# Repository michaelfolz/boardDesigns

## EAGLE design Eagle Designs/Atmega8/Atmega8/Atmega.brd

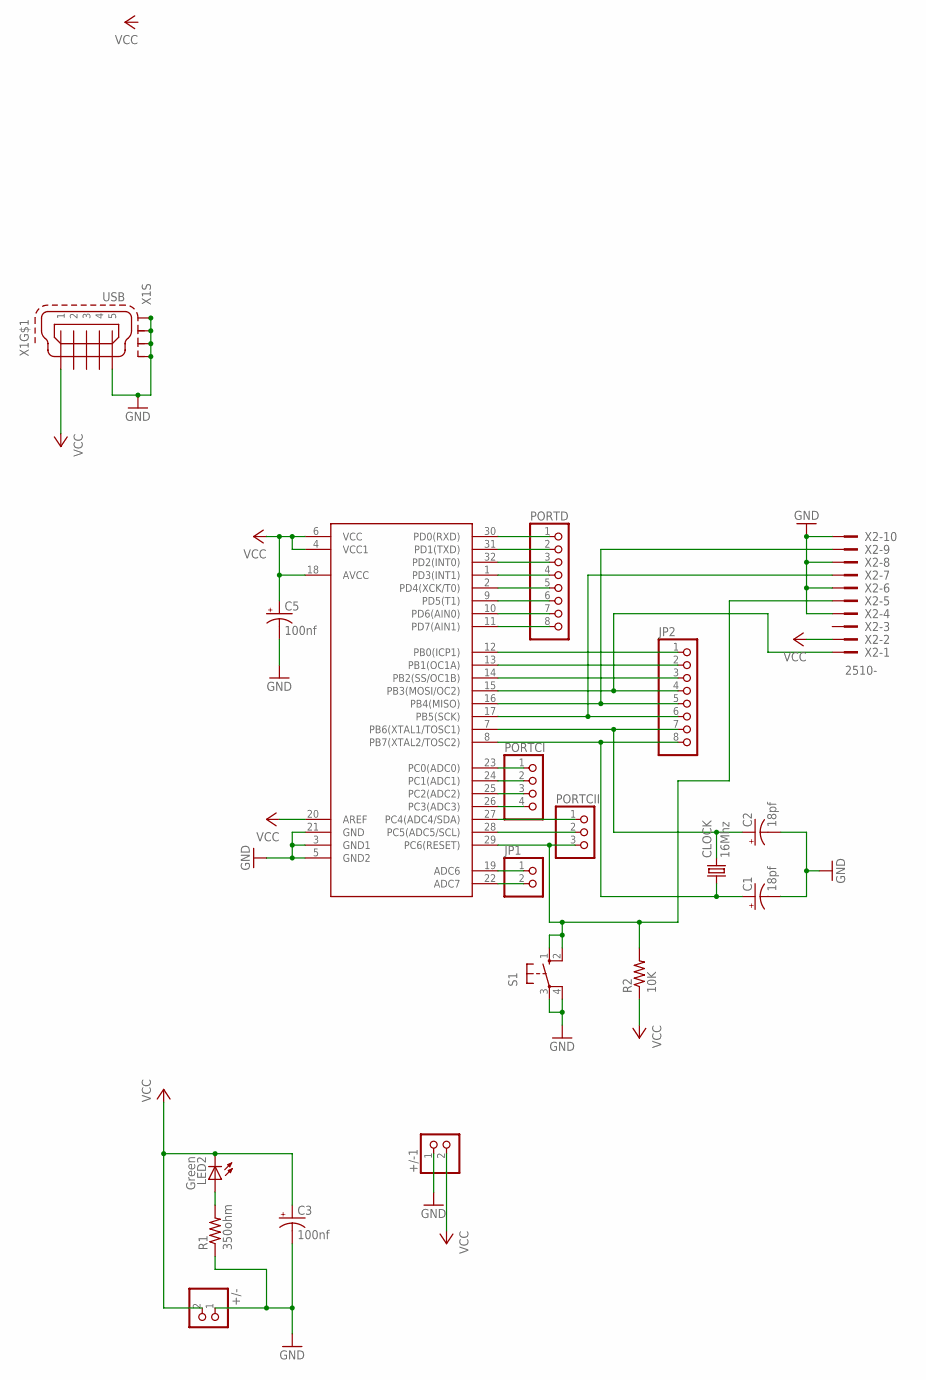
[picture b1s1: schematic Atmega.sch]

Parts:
+/-, +/-1: PINHD-1X2; 1X02
C1, C2: 18pf; SMC_Z
C3, C5: 100nf; SMC_Z
CLOCK: 16Mhz; HC49UP
JP1: PINHD-1X2; 1X02
JP2: PINHD-1X8; 1X08
LED2: Green; PLCC2
PORTCI: PINHD-1X4; 1X04
PORTCII: PINHD-1X3; 1X03
PORTD: PINHD-1X8; 1X08
R1: 350ohm; M0805
R2: 10K; M0805
S1: 10-XX; B3F-10XX
U$1: ATMEGA8A; TQFP32-08
X1: USB; 32005-201
X2: 2510-; PAK100/2500-10

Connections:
GND: +/-.1, +/-1.1, C1.-, C2.-, C3.-, C5.-, R1.1, S1.3, S1.4 (P1), U$1.3 (GND1), U$1.5 (GND2), U$1.21 (GND), X1.5, X1.M1 (S1), X1.M2 (S2), X1.M3 (S3), X1.M4 (S4), X2.4, X2.6, X2.8, X2.10
unnamed: LED2.A, R1.2
unnamed: PORTCI.1, U$1.23 (PC0(ADC0))
unnamed: PORTCI.2, U$1.24 (PC1(ADC1))
unnamed: PORTCI.3, U$1.25 (PC2(ADC2))
unnamed: PORTCI.4, U$1.26 (PC3(ADC3))
unnamed: PORTCII.1, U$1.27 (PC4(ADC4/SDA))
unnamed: PORTCII.2, U$1.28 (PC5(ADC5/SCL))
unnamed: PORTCII.3, R2.2, S1.1 (S), S1.2 (S1), U$1.29 (PC6(RESET)), X2.5
unnamed: JP2.1, U$1.12 (PB0(ICP1))
unnamed: JP2.2, U$1.13 (PB1(OC1A))
unnamed: JP2.3, U$1.14 (PB2(SS/OC1B))
unnamed: JP2.4, U$1.15 (PB3(MOSI/OC2)), X2.1
unnamed: JP2.5, U$1.16 (PB4(MISO)), X2.9
unnamed: JP2.6, U$1.17 (PB5(SCK)), X2.7
unnamed: C2.+, CLOCK.2, JP2.7, U$1.7 (PB6(XTAL1/TOSC1))
unnamed: C1.+, CLOCK.1, JP2.8, U$1.8 (PB7(XTAL2/TOSC2))
unnamed: PORTD.1, U$1.30 (PD0(RXD))
unnamed: PORTD.2, U$1.31 (PD1(TXD))
unnamed: PORTD.3, U$1.32 (PD2(INT0))
unnamed: PORTD.4, U$1.1 (PD3(INT1))
unnamed: PORTD.5, U$1.2 (PD4(XCK/T0))
unnamed: PORTD.6, U$1.9 (PD5(T1))
unnamed: PORTD.7, U$1.10 (PD6(AIN0))
unnamed: PORTD.8, U$1.11 (PD7(AIN1))
unnamed: JP1.1, U$1.19 (ADC6)
unnamed: JP1.2, U$1.22 (ADC7)
VCC: +/-.2, +/-1.2, C3.+, C5.+, LED2.C, R2.1, U$1.4 (VCC1), U$1.6 (VCC), U$1.18 (AVCC), U$1.20 (AREF), X1.1, X2.2

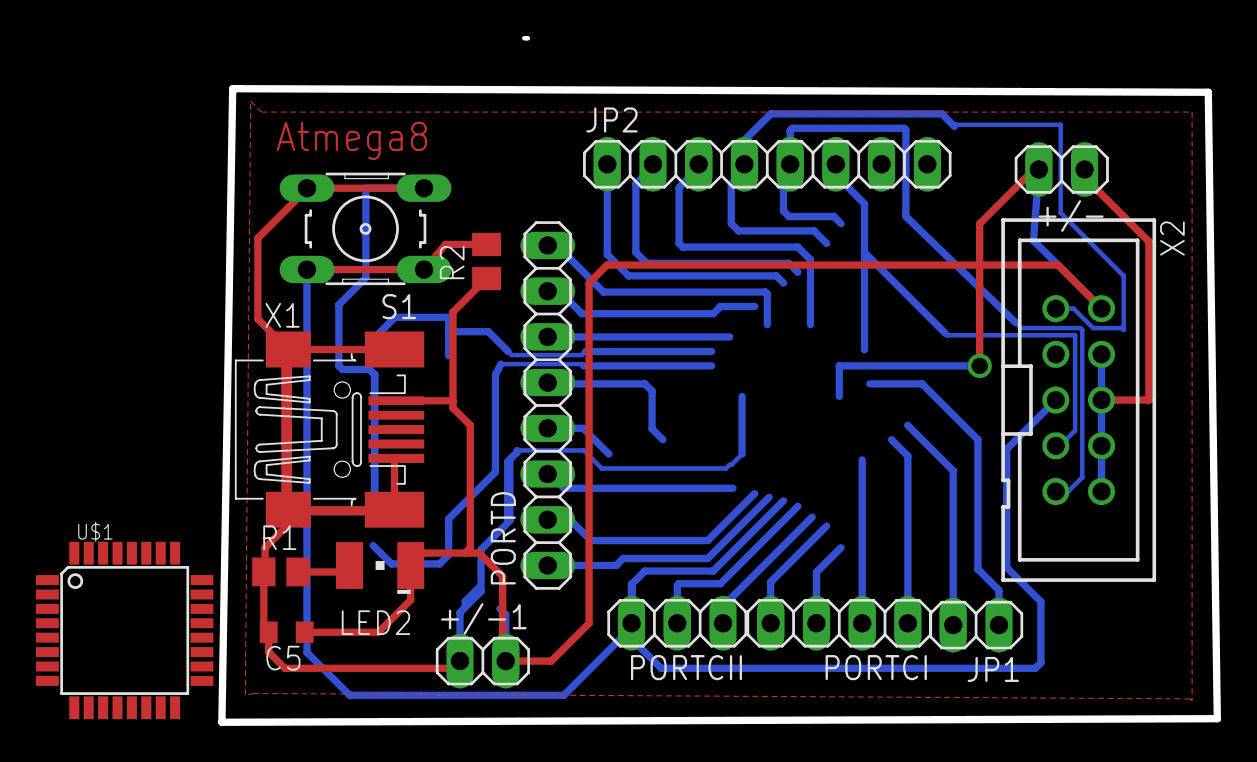
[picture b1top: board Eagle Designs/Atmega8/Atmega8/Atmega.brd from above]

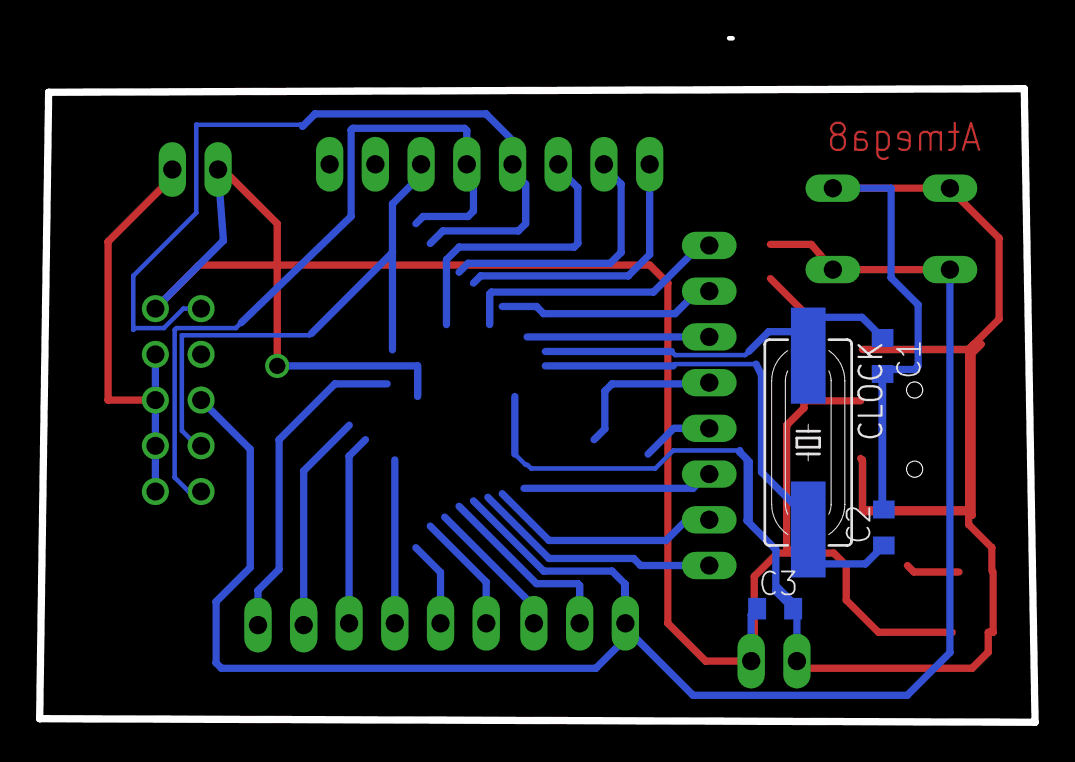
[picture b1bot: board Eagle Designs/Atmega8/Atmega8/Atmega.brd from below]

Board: 2 copper layers, 55.3 x 37.9 mm, 19 parts (4 on the bottom side), 28 nets.

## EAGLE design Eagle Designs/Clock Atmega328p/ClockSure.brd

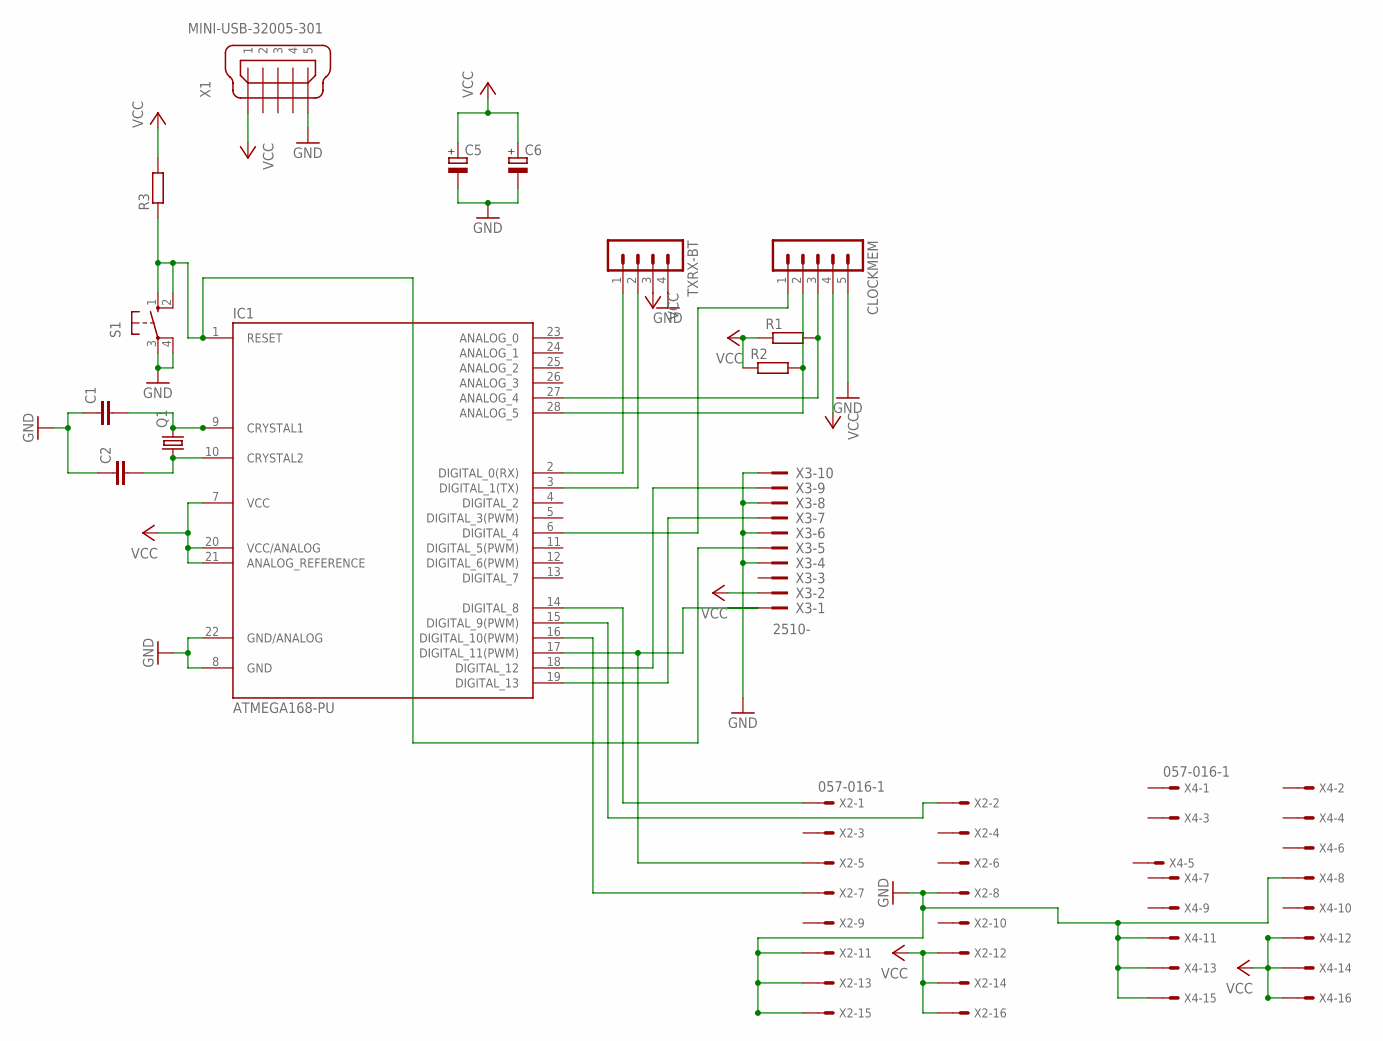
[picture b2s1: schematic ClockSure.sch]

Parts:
C1, C2: C-EU025-030X050; C025-030X050
C5, C6: CPOL-EUE2.5-6; E2,5-6
CLOCKMEM: MA05-1
IC1: ATMEGA168-PU; DIL28-3
Q1: CRYSTALHC49U70; HC49U70
R1, R2, R3: R-EU_0207/10; 0207/10
S1: 10-XX; B3F-10XX
TXRX-BT: MA04-1
X1: MINI-USB-32005-301; 32005-301
X2, X4: 057-016-1
X3: 2510-; PAK100/2500-10

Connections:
GND: C1.1, C2.1, C5.-, C6.-, CLOCKMEM.5, IC1.8 (GND), IC1.22 (GND/ANALOG), S1.3, S1.4 (P1), TXRX-BT.4, X1.5, X2.8, X2.11, X2.13, X2.15, X3.4, X3.6, X3.8, X3.10, X4.8, X4.11, X4.13, X4.15
unnamed: C1.2, IC1.9 (CRYSTAL1), Q1.2
unnamed: C2.2, IC1.10 (CRYSTAL2), Q1.1
unnamed: IC1.2 (DIGITAL_0(RX)), TXRX-BT.1
unnamed: IC1.3 (DIGITAL_1(TX)), TXRX-BT.2
unnamed: CLOCKMEM.2, IC1.28 (ANALOG_5), R2.2
unnamed: IC1.1 (RESET), R3.1, S1.1 (S), S1.2 (S1), X3.5
unnamed: CLOCKMEM.3, IC1.27 (ANALOG_4), R1.2
unnamed: IC1.18 (DIGITAL_12), X3.9
unnamed: IC1.19 (DIGITAL_13), X3.7
unnamed: IC1.17 (DIGITAL_11(PWM)), X2.5, X3.1
unnamed: IC1.15 (DIGITAL_9(PWM)), X2.2
unnamed: IC1.14 (DIGITAL_8), X2.1
unnamed: CLOCKMEM.1, IC1.6 (DIGITAL_4)
unnamed: IC1.16 (DIGITAL_10(PWM)), X2.7
VCC: C5.+, C6.+, CLOCKMEM.4, IC1.7 (VCC), IC1.20 (VCC/ANALOG), IC1.21 (ANALOG_REFERENCE), R1.1, R2.1, R3.2, TXRX-BT.3, X1.1, X2.12, X2.14, X2.16, X3.2, X4.12, X4.14, X4.16

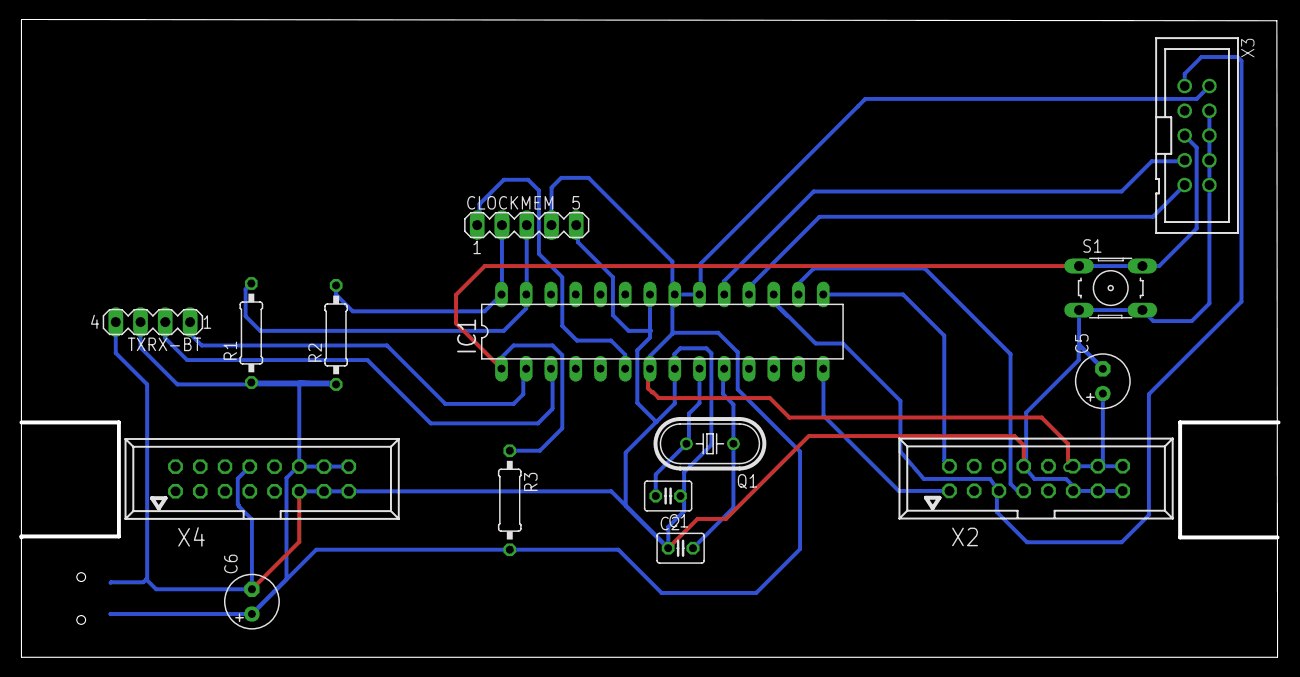
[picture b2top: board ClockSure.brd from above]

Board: 2 copper layers, 129.0 x 65.0 mm, 16 parts (1 on the bottom side), 16 nets.

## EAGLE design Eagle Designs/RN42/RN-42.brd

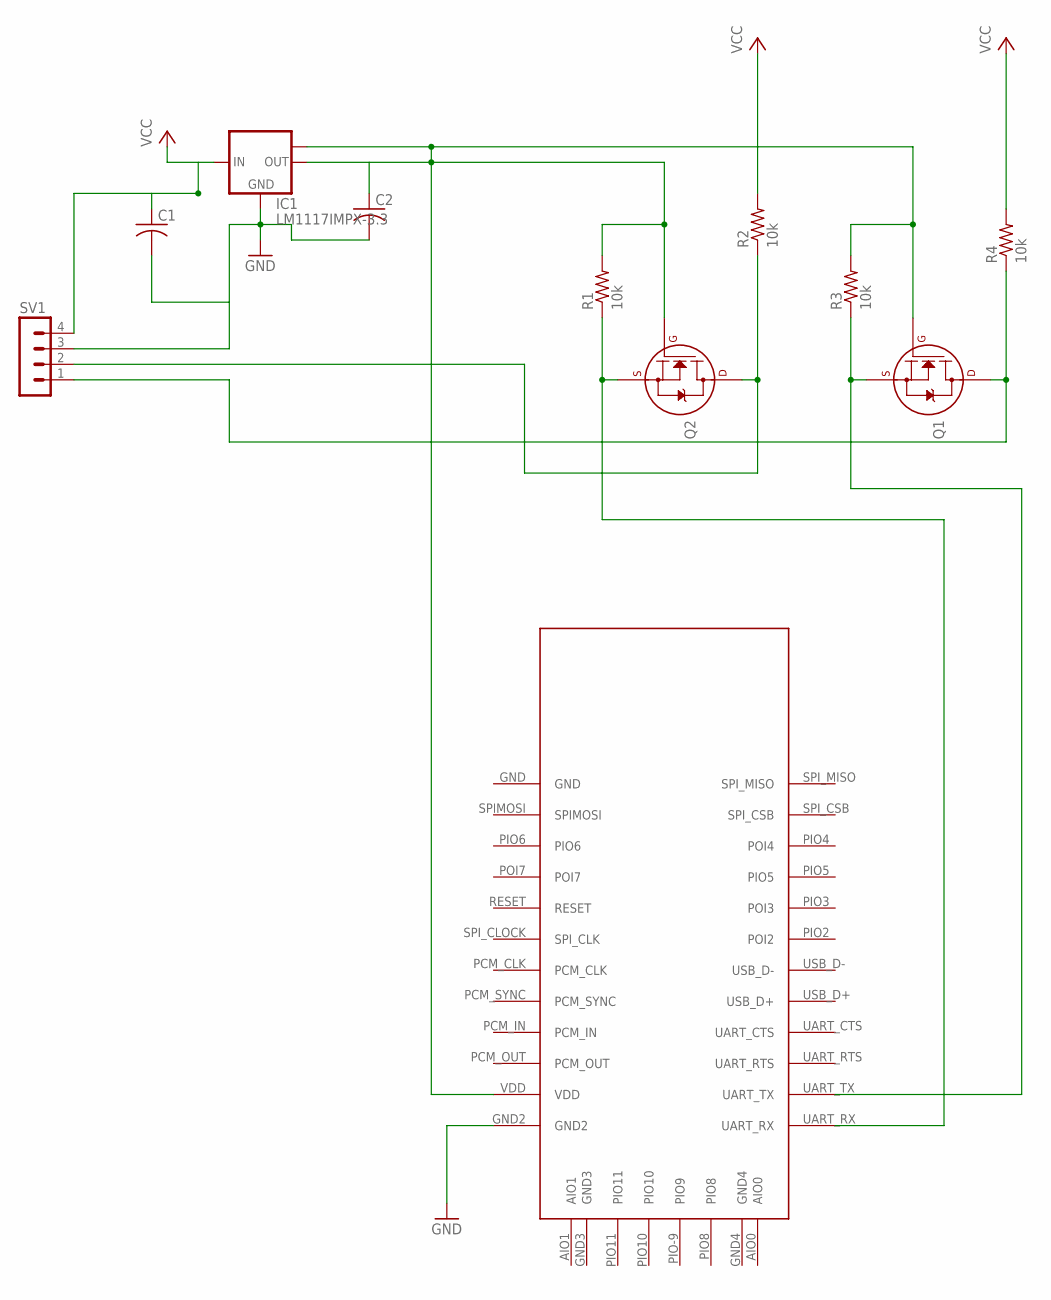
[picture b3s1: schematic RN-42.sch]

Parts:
C1, C2: C-USC0805; C0805
IC1: LM1117IMPX-3.3; SOT223
Q1, Q2: 2N7002_SOT23; SOT-23
R1, R2, R3, R4: 10k; M0805
SV1: MA04-1
U$1: RN-42

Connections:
GND: C1.2, C2.2, IC1.1 (GND), SV1.3, U$1.GND2
unnamed: Q2.2 (S), R1.1, U$1.UART_RX
unnamed: Q2.3 (D), R2.1, SV1.2
unnamed: Q1.2 (S), R3.1, U$1.UART_TX
unnamed: Q1.3 (D), R4.1, SV1.1
unnamed: C2.1, IC1.2 (OUT), IC1.TAB (OUT1), Q1.1 (G), Q2.1 (G), R1.2, R3.2, U$1.VDD
VCC: C1.1, IC1.3 (IN), R2.2, R4.2, SV1.4

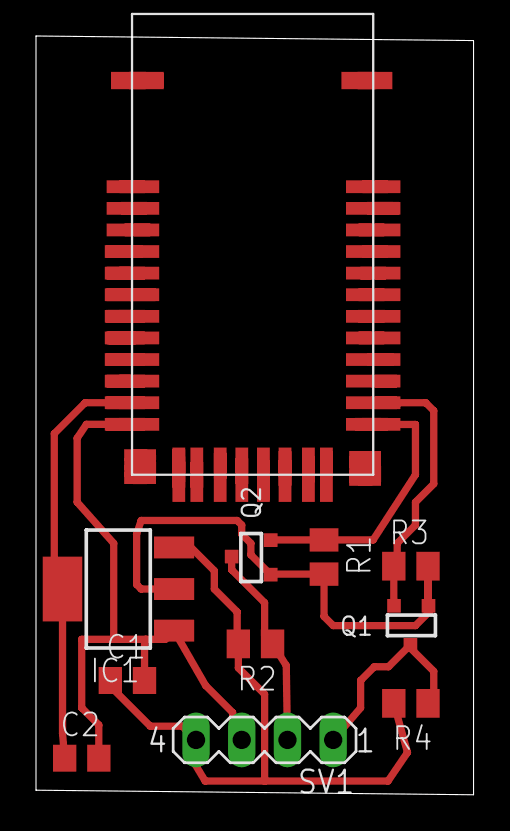
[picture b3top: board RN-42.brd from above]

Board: 2 copper layers, 24.3 x 42.2 mm, 11 parts (0 on the bottom side), 7 nets.

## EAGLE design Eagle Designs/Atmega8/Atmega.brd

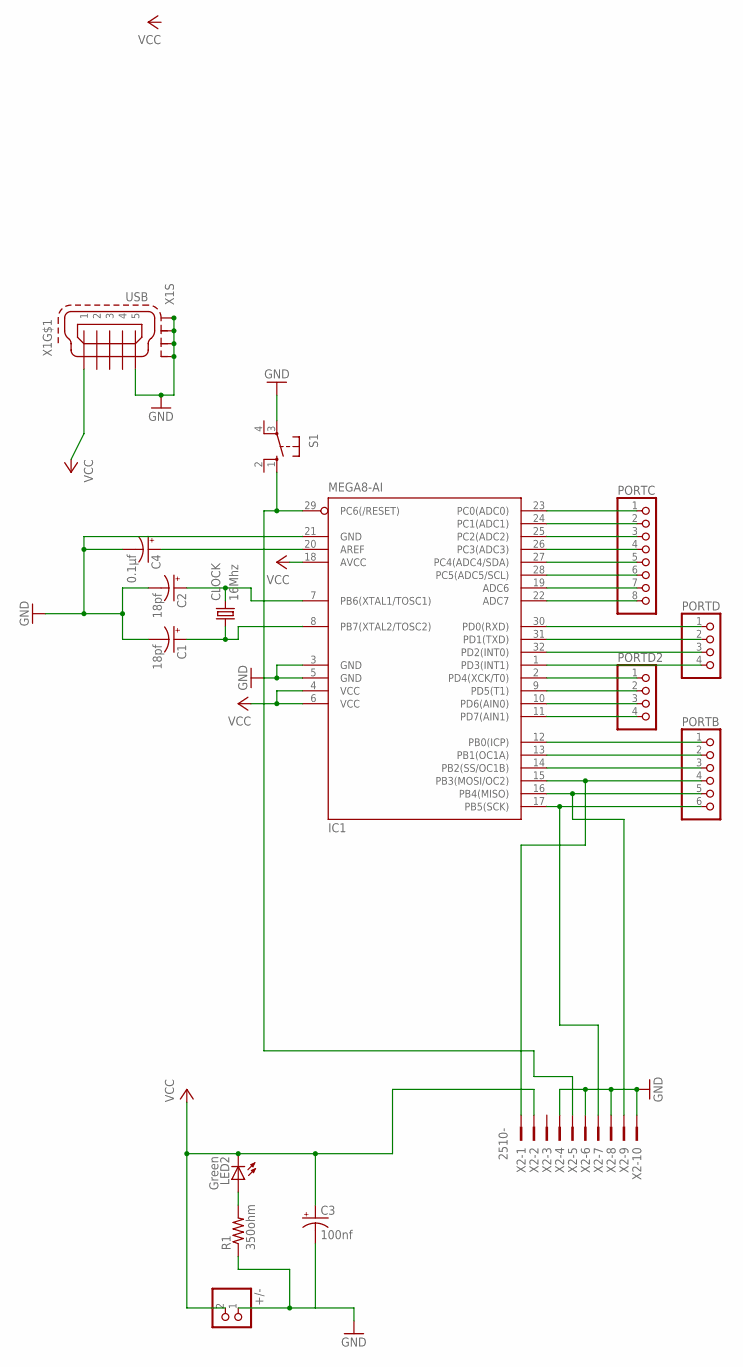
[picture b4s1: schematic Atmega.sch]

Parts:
+/-: PINHD-1X2; 1X02
C1, C2: 18pf; SMC_Z
C3: 100nf; SMC_Z
C4: 0.1µf; SMC_Z
CLOCK: 16Mhz; HC49UP
IC1: MEGA8-AI; TQFP32-08
LED2: Green; PLCC2
PORTB: PINHD-1X6; 1X06
PORTC: PINHD-1X8; 1X08
PORTD, PORTD2: PINHD-1X4; 1X04
R1: 350ohm; M0805
S1: 10-XX; B3F-10XX
X1: USB; 32005-201
X2: 2510-; PAK100/2500-10

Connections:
GND: +/-.1, C1.-, C2.-, C3.-, C4.-, IC1.3 (GND), IC1.5 (GND), IC1.21 (GND), R1.1, S1.3, X1.5, X1.M1 (S1), X1.M2 (S2), X1.M3 (S3), X1.M4 (S4), X2.4, X2.6, X2.8, X2.10
unnamed: C2.+, CLOCK.2, IC1.7 (PB6(XTAL1/TOSC1))
unnamed: IC1.29 (PC6(/RESET)), S1.1 (S), X2.5
unnamed: IC1.30 (PD0(RXD)), PORTD.1
unnamed: LED2.A, R1.2
unnamed: IC1.23 (PC0(ADC0)), PORTC.1
unnamed: IC1.24 (PC1(ADC1)), PORTC.2
unnamed: C1.+, CLOCK.1, IC1.8 (PB7(XTAL2/TOSC2))
unnamed: IC1.25 (PC2(ADC2)), PORTC.3
unnamed: IC1.26 (PC3(ADC3)), PORTC.4
unnamed: IC1.27 (PC4(ADC4/SDA)), PORTC.5
unnamed: IC1.28 (PC5(ADC5/SCL)), PORTC.6
unnamed: IC1.19 (ADC6), PORTC.7
unnamed: IC1.22 (ADC7), PORTC.8
unnamed: IC1.31 (PD1(TXD)), PORTD.2
unnamed: IC1.32 (PD2(INT0)), PORTD.3
unnamed: IC1.1 (PD3(INT1)), PORTD.4
unnamed: IC1.2 (PD4(XCK/T0)), PORTD2.1
unnamed: IC1.9 (PD5(T1)), PORTD2.2
unnamed: IC1.10 (PD6(AIN0)), PORTD2.3
unnamed: IC1.11 (PD7(AIN1)), PORTD2.4
unnamed: IC1.12 (PB0(ICP)), PORTB.1
unnamed: IC1.13 (PB1(OC1A)), PORTB.2
unnamed: IC1.14 (PB2(SS/OC1B)), PORTB.3
unnamed: IC1.15 (PB3(MOSI/OC2)), PORTB.4, X2.1
unnamed: IC1.16 (PB4(MISO)), PORTB.5, X2.9
unnamed: IC1.17 (PB5(SCK)), PORTB.6, X2.7
unnamed: C4.+, IC1.20 (AREF)
VCC: +/-.2, C3.+, IC1.4 (VCC), IC1.6 (VCC), IC1.18 (AVCC), LED2.C, X1.1, X1.4, X2.2

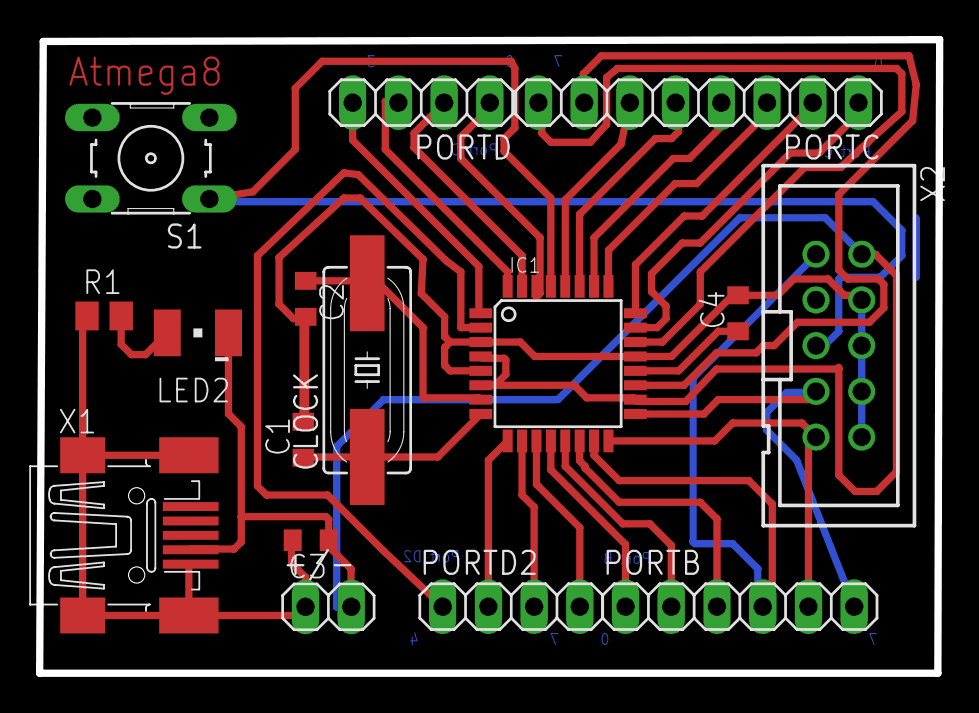
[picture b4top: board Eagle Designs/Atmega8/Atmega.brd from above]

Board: 2 copper layers, 50.0 x 35.2 mm, 16 parts (0 on the bottom side), 29 nets.

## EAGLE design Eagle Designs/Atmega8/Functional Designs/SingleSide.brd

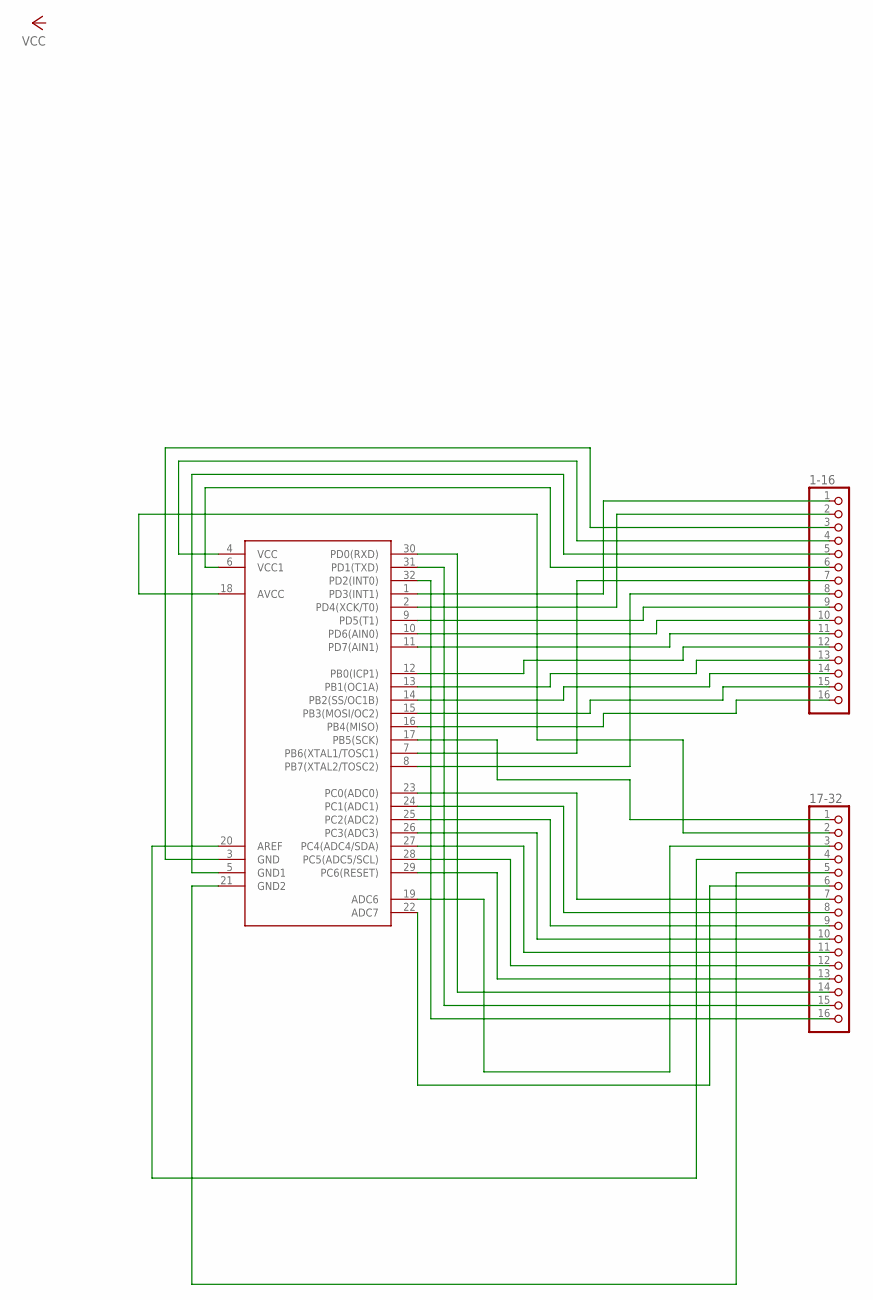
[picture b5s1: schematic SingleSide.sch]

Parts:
1-16, 17-32: PINHD-1X16; 1X16
U$1: ATMEGA8A; TQFP32-08

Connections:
unnamed: 1-16.1, U$1.1 (PD3(INT1))
unnamed: 1-16.2, U$1.2 (PD4(XCK/T0))
unnamed: 1-16.3, U$1.3 (GND)
unnamed: 1-16.4, U$1.4 (VCC)
unnamed: 1-16.5, U$1.5 (GND1)
unnamed: 1-16.6, U$1.6 (VCC1)
unnamed: 1-16.7, U$1.7 (PB6(XTAL1/TOSC1))
unnamed: 1-16.8, U$1.8 (PB7(XTAL2/TOSC2))
unnamed: 1-16.9, U$1.9 (PD5(T1))
unnamed: 1-16.10, U$1.10 (PD6(AIN0))
unnamed: 1-16.11, U$1.11 (PD7(AIN1))
unnamed: 1-16.12, U$1.12 (PB0(ICP1))
unnamed: 1-16.13, U$1.13 (PB1(OC1A))
unnamed: 1-16.14, U$1.14 (PB2(SS/OC1B))
unnamed: 1-16.15, U$1.15 (PB3(MOSI/OC2))
unnamed: 1-16.16, U$1.16 (PB4(MISO))
unnamed: 17-32.2, U$1.18 (AVCC)
unnamed: 17-32.16, U$1.32 (PD2(INT0))
unnamed: 17-32.14, U$1.30 (PD0(RXD))
unnamed: 17-32.13, U$1.29 (PC6(RESET))
unnamed: 17-32.12, U$1.28 (PC5(ADC5/SCL))
unnamed: 17-32.11, U$1.27 (PC4(ADC4/SDA))
unnamed: 17-32.10, U$1.26 (PC3(ADC3))
unnamed: 17-32.9, U$1.25 (PC2(ADC2))
unnamed: 17-32.8, U$1.24 (PC1(ADC1))
unnamed: 17-32.7, U$1.23 (PC0(ADC0))
unnamed: 17-32.15, U$1.31 (PD1(TXD))
unnamed: 17-32.6, U$1.22 (ADC7)
unnamed: 17-32.3, U$1.19 (ADC6)
unnamed: 17-32.4, U$1.20 (AREF)
unnamed: 17-32.5, U$1.21 (GND2)
unnamed: 17-32.1, U$1.17 (PB5(SCK))

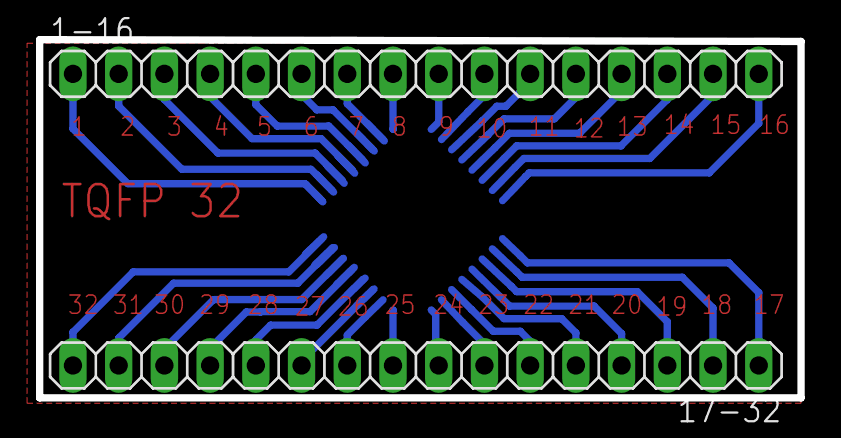
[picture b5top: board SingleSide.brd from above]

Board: 2 copper layers, 42.3 x 19.9 mm, 3 parts (1 on the bottom side), 32 nets.

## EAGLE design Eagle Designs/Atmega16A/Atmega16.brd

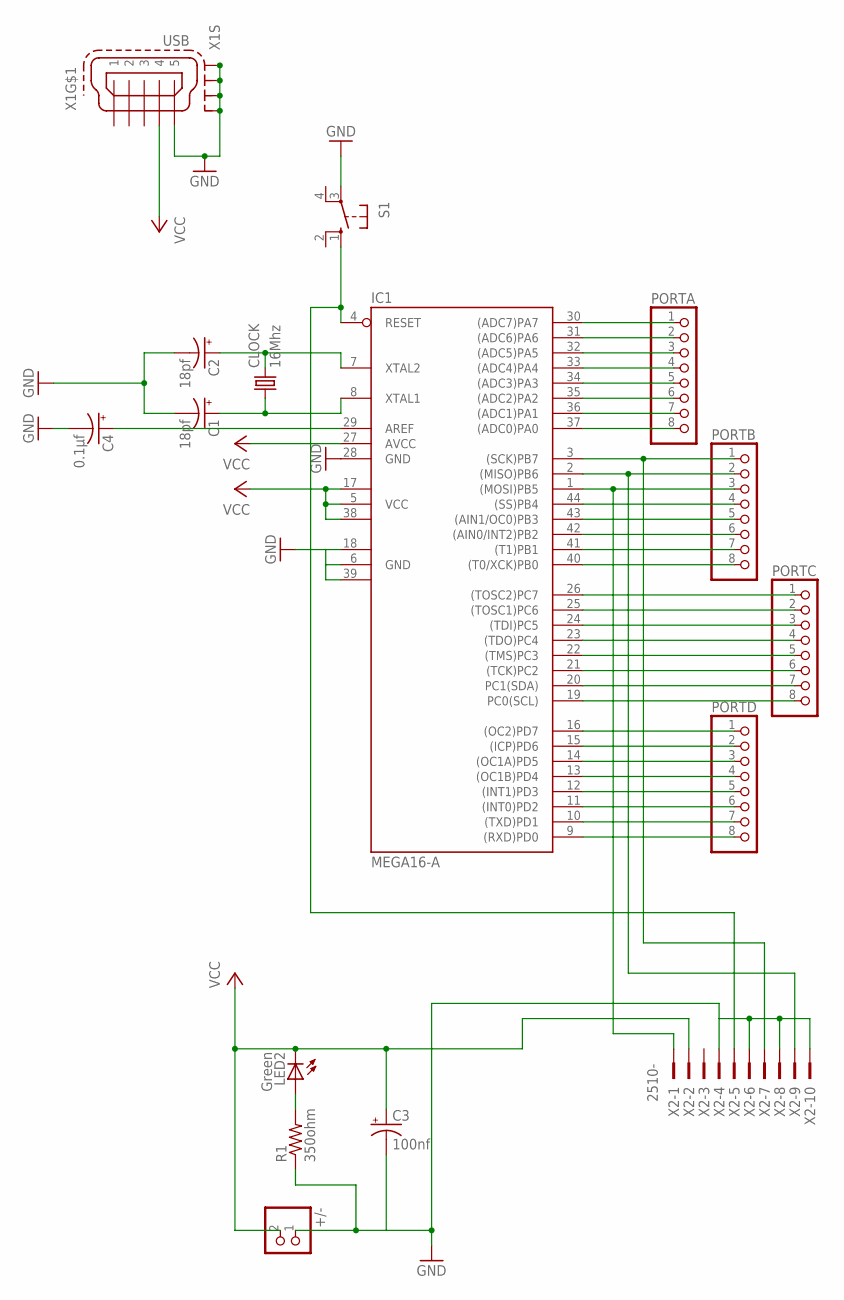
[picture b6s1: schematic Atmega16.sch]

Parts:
+/-: PINHD-1X2; 1X02
C1, C2: 18pf; SMC_Z
C3: 100nf; SMC_Z
C4: 0.1µf; SMC_Z
CLOCK: 16Mhz; HC49UP
IC1: MEGA16-A; TQFP44
LED2: Green; PLCC2
PORTA: PINHD-1X8; 1X08
PORTB: PINHD-1X8; 1X08
PORTC: PINHD-1X8; 1X08
PORTD: PINHD-1X8; 1X08
R1: 350ohm; M0805
S1: 10-XX; B3F-10XX
X1: USB; 32005-201
X2: 2510-; PAK100/2500-10

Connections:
GND: +/-.1, C1.-, C2.-, C3.-, C4.-, IC1.6 (GND), IC1.18 (GND1), IC1.28 (GND), IC1.39 (GND2), R1.1, S1.3, X1.5, X1.M1 (S1), X1.M2 (S2), X1.M3 (S3), X1.M4 (S4), X2.4, X2.6, X2.8, X2.10
unnamed: C2.+, CLOCK.2, IC1.7 (XTAL2)
unnamed: IC1.16 ((OC2)PD7), PORTD.1
unnamed: S1.1 (S), X2.5
unnamed: LED2.A, R1.2
unnamed: IC1.15 ((ICP)PD6), PORTD.2
unnamed: IC1.14 ((OC1A)PD5), PORTD.3
unnamed: C1.+, CLOCK.1, IC1.8 (XTAL1)
unnamed: C4.+, IC1.29 (AREF)
unnamed: IC1.13 ((OC1B)PD4), PORTD.4
unnamed: IC1.12 ((INT1)PD3), PORTD.5
unnamed: IC1.11 ((INT0)PD2), PORTD.6
unnamed: IC1.10 ((TXD)PD1), PORTD.7
unnamed: IC1.9 ((RXD)PD0), PORTD.8
unnamed: IC1.26 ((TOSC2)PC7), PORTC.1
unnamed: IC1.25 ((TOSC1)PC6), PORTC.2
unnamed: IC1.24 ((TDI)PC5), PORTC.3
unnamed: IC1.23 ((TDO)PC4), PORTC.4
unnamed: IC1.22 ((TMS)PC3), PORTC.5
unnamed: IC1.21 ((TCK)PC2), PORTC.6
unnamed: IC1.20 (PC1(SDA)), PORTC.7
unnamed: IC1.19 (PC0(SCL)), PORTC.8
unnamed: IC1.3 ((SCK)PB7), PORTB.1, X2.7
unnamed: IC1.2 ((MISO)PB6), PORTB.2, X2.9
unnamed: IC1.1 ((MOSI)PB5), PORTB.3, X2.1
unnamed: IC1.44 ((SS)PB4), PORTB.4
unnamed: IC1.43 ((AIN1/OC0)PB3), PORTB.5
unnamed: IC1.42 ((AIN0/INT2)PB2), PORTB.6
unnamed: IC1.41 ((T1)PB1), PORTB.7
unnamed: IC1.40 ((T0/XCK)PB0), PORTB.8
unnamed: IC1.30 ((ADC7)PA7), PORTA.1
unnamed: IC1.31 ((ADC6)PA6), PORTA.2
unnamed: IC1.32 ((ADC5)PA5), PORTA.3
unnamed: IC1.33 ((ADC4)PA4), PORTA.4
unnamed: IC1.34 ((ADC3)PA3), PORTA.5
unnamed: IC1.35 ((ADC2)PA2), PORTA.6
unnamed: IC1.36 ((ADC1)PA1), PORTA.7
unnamed: IC1.37 ((ADC0)PA0), PORTA.8
VCC: +/-.2, C3.+, IC1.5 (VCC), IC1.17 (VCC1), IC1.27 (AVCC), IC1.38 (VCC2), LED2.C, X1.4, X2.2

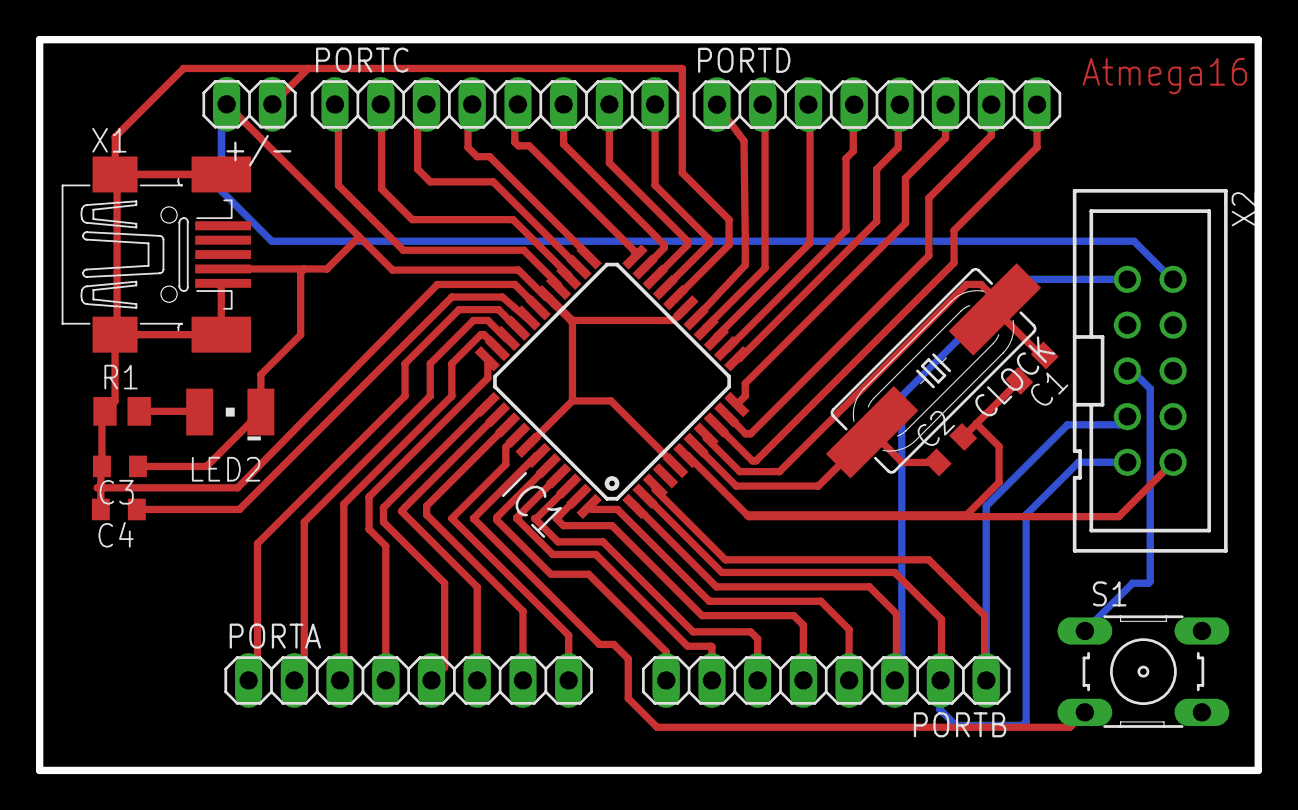
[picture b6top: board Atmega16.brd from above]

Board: 2 copper layers, 67.7 x 40.6 mm, 16 parts (0 on the bottom side), 39 nets.

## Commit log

2017-09-11 added board designs
